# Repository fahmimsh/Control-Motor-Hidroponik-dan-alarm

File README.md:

# Control_Motor_Hidroponik-dan-alarm
motor control for hydroponic plants with pH sensor feedback and using a fertilizer application time alarm to remind users

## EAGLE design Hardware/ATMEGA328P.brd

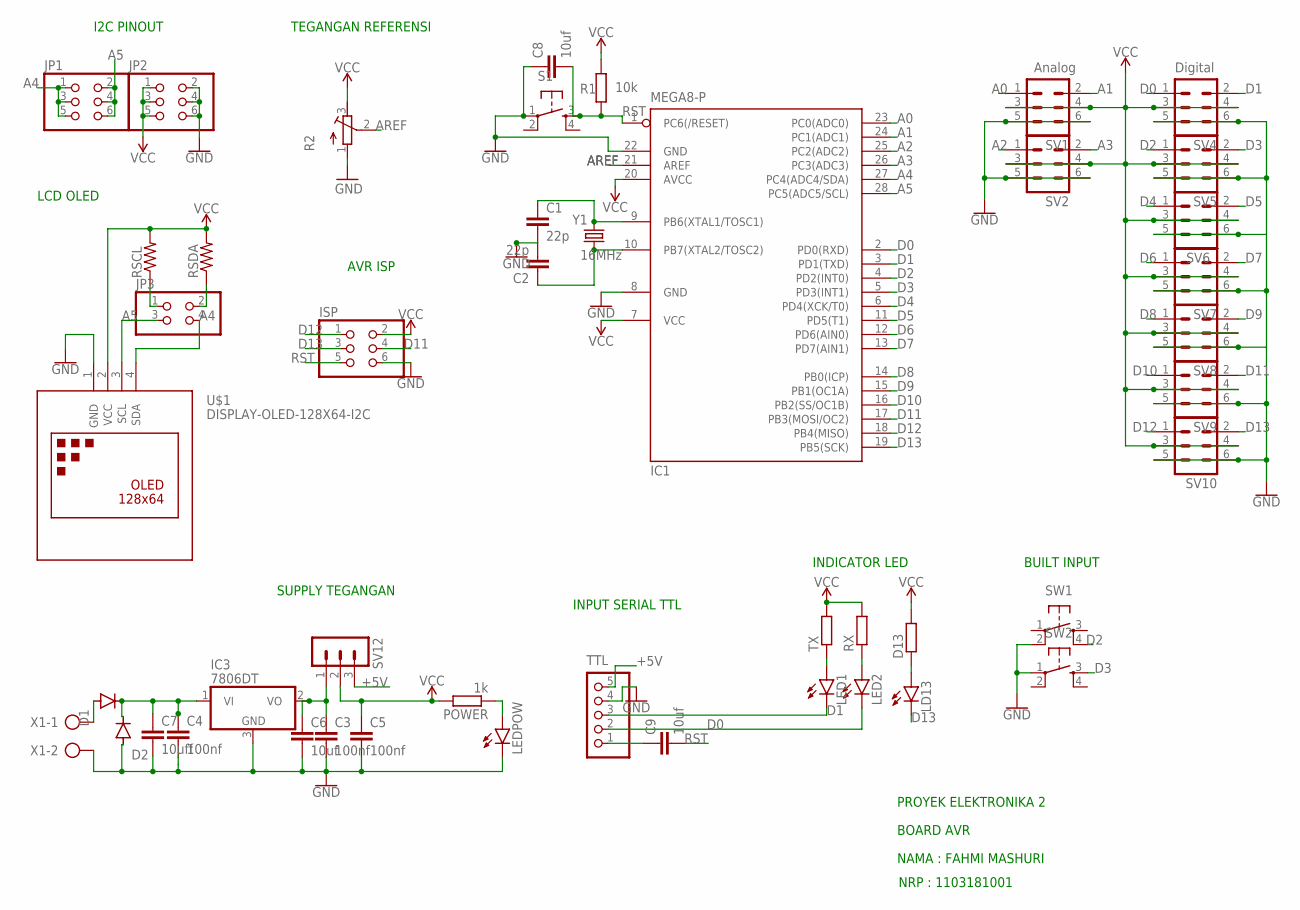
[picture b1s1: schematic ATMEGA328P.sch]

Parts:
C1, C2: 22p; C0805K
C3, C4, C5: 100nf; C0805K
C6, C8, C9: 10uf; C0805K
C7: 10uff; C0805K
D1, D2: PURPLE; SOD80C
D13: R-EU_R0805; R0805
IC1: MEGA8-P; DIL28-3
IC3: 7806DT; TO252
ISP: PINHD-2X3; 2X03
JP1, JP2: PINHD-2X3; 2X03
JP3: PINHD-2X2; 2X02
LD13: LED3MM
LED1, LED2: LED3MM
LEDPOW: LED3MM
POWER: 1k; R0805
R1: 10k; R0805
R2: R-TRIMM64W; RTRIM64W
RSCL: R-US_R1206; R1206
RSDA: R-US_R1206; R1206
RX: R-EU_R0805; R0805
S1: TAC_SWITCHPTH; TACTILE-PTH
SV1, SV2, SV4, SV5, SV6, SV7, SV8, SV9, SV10: MA03-2
SV12: MA03-1
SW1, SW2: TAC_SWITCHPTH; TACTILE-PTH
TTL: PINHD-1X5; 1X05
TX: R-EU_R0805; R0805
U$1: DISPLAY-OLED-128X64-I2C
X1: AK500/2-H
Y1: 16MHz; HC49UP

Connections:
+5V: SV12.3, TTL.5
A0: IC1.23 (PC0(ADC0)), SV1.1
A1: IC1.24 (PC1(ADC1)), SV1.2
A2: IC1.25 (PC2(ADC2)), SV2.1
A3: IC1.26 (PC3(ADC3)), SV2.2
A4: IC1.27 (PC4(ADC4/SDA)), JP1.1, JP1.3, JP1.5, JP3.4, U$1.4 (SDA)
A5: IC1.28 (PC5(ADC5/SCL)), JP1.2, JP1.4, JP1.6, JP3.3, U$1.3 (SCL)
AREF: IC1.21 (AREF), R2.2 (S)
D0: IC1.2 (PD0(RXD)), LED2.K (C), SV4.1, TTL.2
D1: IC1.3 (PD1(TXD)), LED1.K (C), SV4.2, TTL.3
D2: IC1.4 (PD2(INT0)), SV5.1, SW1.4
D3: IC1.5 (PD3(INT1)), SV5.2, SW2.3
D4: IC1.6 (PD4(XCK/T0)), SV6.1
D5: IC1.11 (PD5(T1)), SV6.2
D6: IC1.12 (PD6(AIN0)), SV7.1
D7: IC1.13 (PD7(AIN1)), SV7.2
D8: IC1.14 (PB0(ICP)), SV8.1
D9: IC1.15 (PB1(OC1A)), SV8.2
D10: IC1.16 (PB2(SS/OC1B)), SV9.1
D11: IC1.17 (PB3(MOSI/OC2)), ISP.4, SV9.2
D12: IC1.18 (PB4(MISO)), ISP.1, SV10.1
D13: IC1.19 (PB5(SCK)), ISP.3, LD13.K (C), SV10.2
GND: C1.2, C2.2, C3.2, C4.2, C5.2, C6.2, C7.2, C8.1, D2.A, IC1.8 (GND), IC1.22 (GND), IC3.3 (GND), ISP.6, JP2.2, JP2.4, JP2.6, LEDPOW.K (C), R2.1 (A), S1.1, SV1.5, SV1.6, SV2.5, SV2.6, SV4.5, SV4.6, SV5.5, SV5.6, SV6.5, SV6.6, SV7.5, SV7.6, SV8.5, SV8.6, SV9.5, SV9.6, SV10.5, SV10.6, SW1.2, SW2.1, TTL.4, U$1.1 (GND), X1.2
unnamed: D13.1, LD13.A
unnamed: C9.1, TTL.1
unnamed: JP3.1, RSCL.1
unnamed: JP3.2, RSDA.1
unnamed: C1.1, IC1.9 (PB6(XTAL1/TOSC1)), Y1.2
unnamed: C2.1, IC1.10 (PB7(XTAL2/TOSC2)), Y1.1
unnamed: D1.A, X1.1
unnamed: C4.1, C7.1, D1.C, D2.C, IC3.1 (VI)
unnamed: LED1.A, TX.1
unnamed: LED2.A, RX.1
unnamed: C3.1, C6.1, IC3.2 (VO), SV12.1
unnamed: LEDPOW.A, POWER.1
RST: C8.2, C9.2, IC1.1 (PC6(/RESET)), ISP.5, R1.1, S1.3
VCC: C5.1, D13.2, IC1.7 (VCC), IC1.20 (AVCC), ISP.2, JP2.1, JP2.3, JP2.5, POWER.2, R1.2, R2.3 (E), RSCL.2, RSDA.2, RX.2, SV1.3, SV1.4, SV2.3, SV2.4, SV4.3, SV4.4, SV5.3, SV5.4, SV6.3, SV6.4, SV7.3, SV7.4, SV8.3, SV8.4, SV9.3, SV9.4, SV10.3, SV10.4, SV12.2, TX.2, U$1.2 (VCC)

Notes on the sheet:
Analog
Digital
LCD OLED
SUPPLY TEGANGAN
TEGANGAN REFERENSI
INPUT SERIAL TTL
AVR ISP
INDICATOR LED
BUILT INPUT
I2C PINOUT
PROYEK ELEKTRONIKA 2
BOARD AVR
NAMA : FAHMI MASHURI
NRP : 1103181001

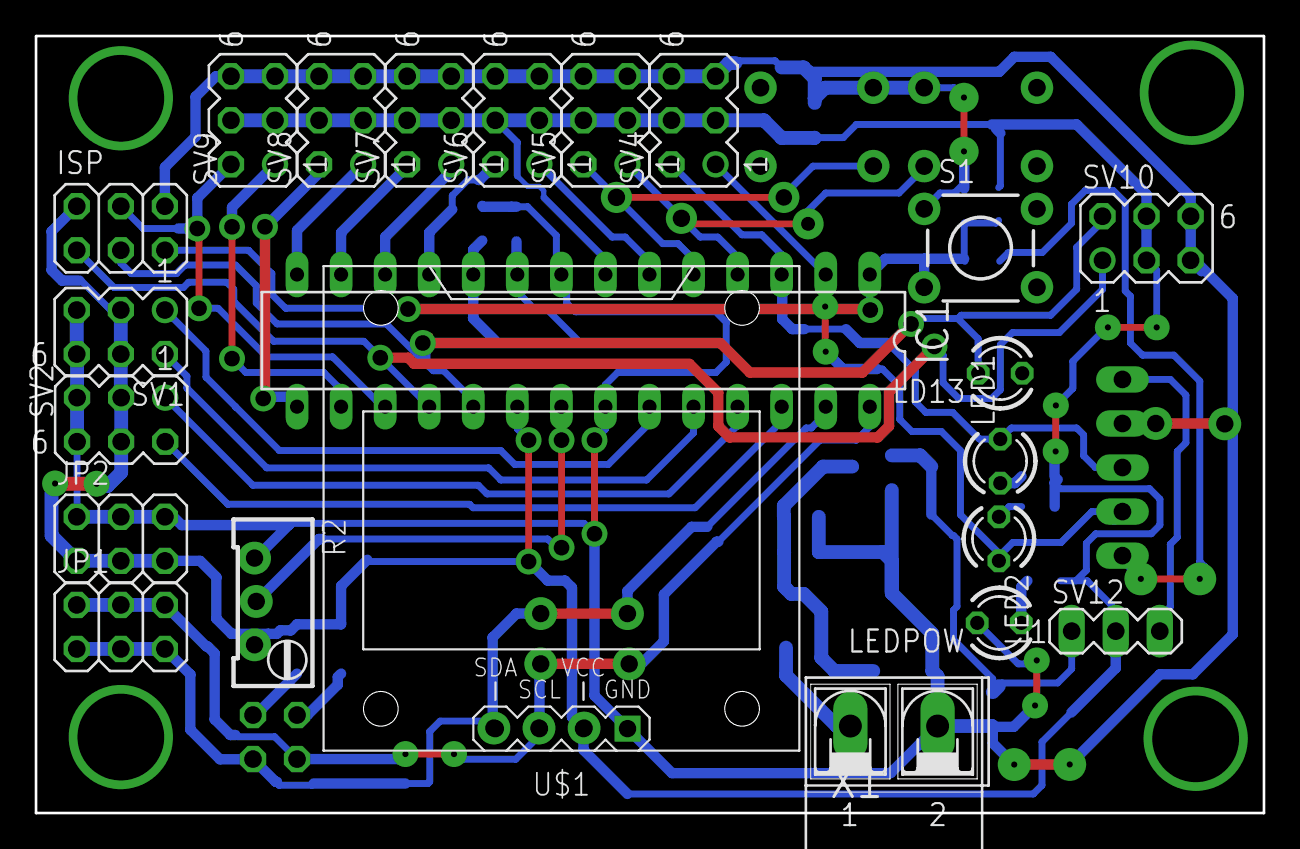
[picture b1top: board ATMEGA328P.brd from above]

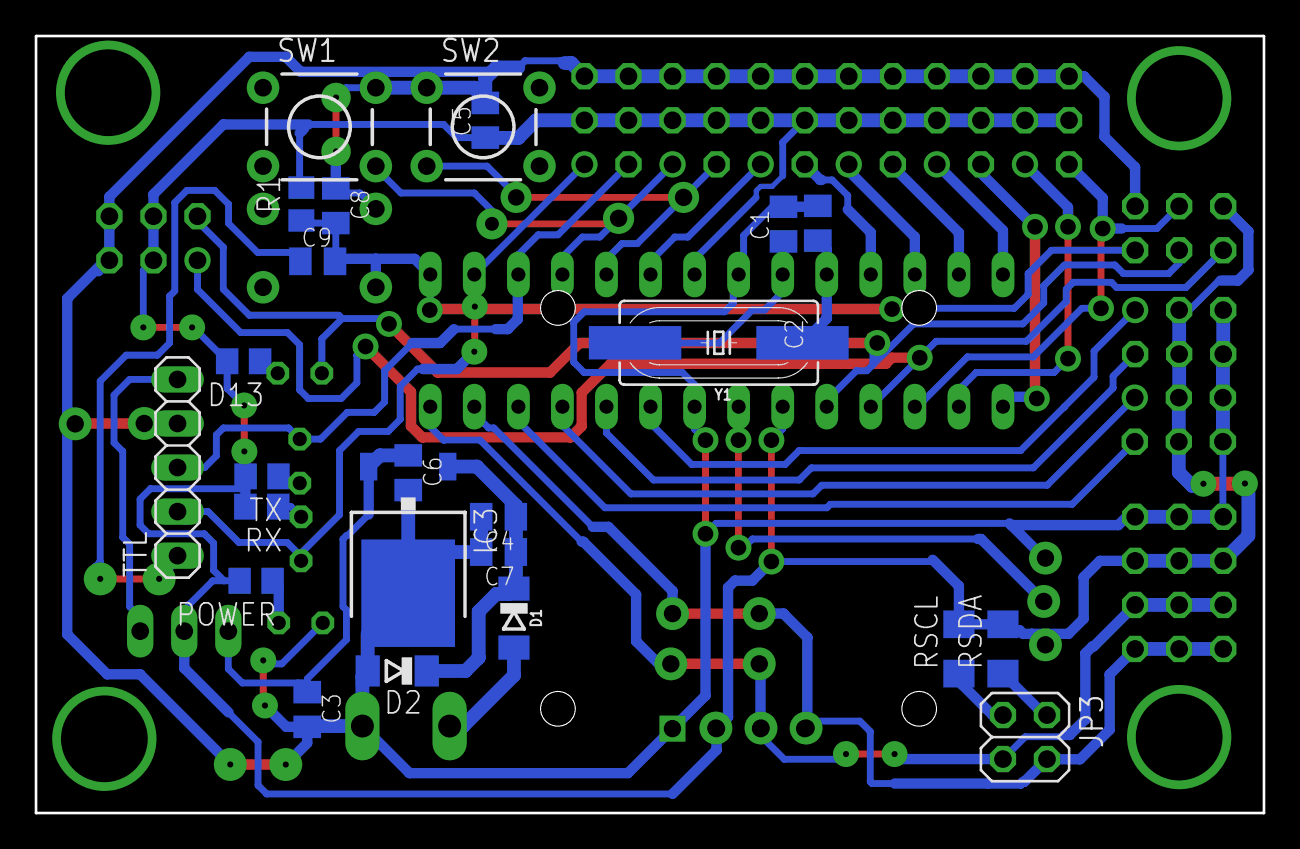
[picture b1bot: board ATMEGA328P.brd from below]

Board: 2 copper layers, 70.8 x 44.8 mm, 46 parts (24 on the bottom side), 37 nets.

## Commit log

2020-09-20 projek ke3

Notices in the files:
parts and their libraries:
SparkFun-Retired: Licensing: Creative Commons ShareAlike 4.0 International - https://creativecommons.org/licenses/by-sa/4.0
oled lcd: Released under the Creative Commons Attribution 4.0 International License: http://creativecommons.org/licenses/by/4.0
